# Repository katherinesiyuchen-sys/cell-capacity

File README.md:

# Cell Capacity Tester
An Arduino-based constant-current discharge tester for 18650 lithium cells. It pulls a selected/controlled current out of a cell and 
integrates that current over time to compute the cell's true capacity in mAh, with live readout on an OLED and automatic thermal cutoff for safety.

## How it works
The circuitry is a constant-current electronic load with an op-amp continuously adjusts a MOSFET's gate voltage to hold a selected discharge current steady 
regardless of the cell's falling voltage. By integrating that known current over time, the firmware accumulates total charge delivered, the cell's capacity, by multiplying the time and current.

## Circuit Overview
### Power system
BT1 (the 18650 cell) is the sole power source at ~3.6–4.2 V. Current flows from the positive terminal through **F1** (4 A resettable polyfuse) 
and **D1** (Schottky diode, low forward drop, blocks reverse insertion) onto the batt+ net. 
**C1 (100 nF)** and **C2 (220 µF)** in parallel stabilize batt+, where C2 absorbs voltage sags when the MOSFET draws heavy current, C1 filters high-frequency noise.

The Arduino is powered from USB (VUSB) +5V rail, and its 3V3 pin supplies the +3.3 V rail for the OLED.

### Constant-current discharge
- **Q1 (IRLZ44N)**: logic-level MOSFET in series with the load, acting as a variable resistor controlled by gate voltage. Fully on at 3.3–5 V, so it's directly Arduino-drivable.
- **R4A & R4B**: two 1 Ω / 10 W resistors in parallel (0.5 Ω total) as the sense/load resistors. All discharge current flows through them; voltage across them = I × 0.5 Ω.
- **U1A (LM358)**: op-amp in the feedback loop:
  - '–' input (pin 2): actual voltage across the load resistors (i.e. actual current)
  - '+' input (pin 3): filtered PWM from Arduino A2 (target current)
  - The op-amp drives the gate to null the difference: if actual current is too low the gate rises (MOSFET opens more); too high and it closes slightly.
- **R7 (470 Ω)** between op-amp output and gate damps high-frequency oscillation.
- **R3 / C3** form a low-pass RC filter (τ = 10k × 100 n = 1 ms) that smooths the A2 PWM into a steady DC target voltage.

### Current setting
**SW1 (D14)** and **SW2 (D15)** are pulled up to +5 V through R5/R6. Pressing a button pulls the pin to GND; the Arduino detects the falling edge and increases or decreases the A2 PWM duty cycle, 
which changes the target voltage at the op-amp and therefore the set current. SW1 is UP/START — it also begins the test.

### Temperature sensing
**TH1 (10k NTC thermistor)** forms a voltage divider with R2 (10k):
```
TEMP = 5 V × R2 / (R2 + TH1)
```
The Arduino reads TEMP on **A0**. As temperature rises, TH1's resistance drops and TEMP rises. Firmware uses this to cut off the test above a safe threshold. 
Mount TH1 as close to the battery holder as possible so it can be bent to contact the cell.

### OLED display (DS1)
128×64 I²C OLED powered from 3.3 V and displays voltage, current, temperature, and accumulated mAh live during the test.

### Buzzer
Driven directly by the Arduino, beeps on test start, end, and fault.

### Op-amp protection
The LM358 is a dual op-amp. U1A does the constant-current control; the unused sections are wired as unity-gain followers with negative feedback so their inputs aren't left floating 
(floating inputs can be driven to the rails by EMI, causing excess current draw and rail instability). C4 filters VCC into the op-amp.

## Bill of Materials
Full BOM: [Google Sheets](https://docs.google.com/spreadsheets/d/1DATSQ3IbzevVbkfX_8bRBYmYYDkdU8qtv9zlPYZS3Pw/edit?usp=sharing)

All components are sourced from **DigiKey** except the **OLED screen**, which is purchased from Amazon.

## License

Licensed under the [Apache License 2.0](LICENSE).

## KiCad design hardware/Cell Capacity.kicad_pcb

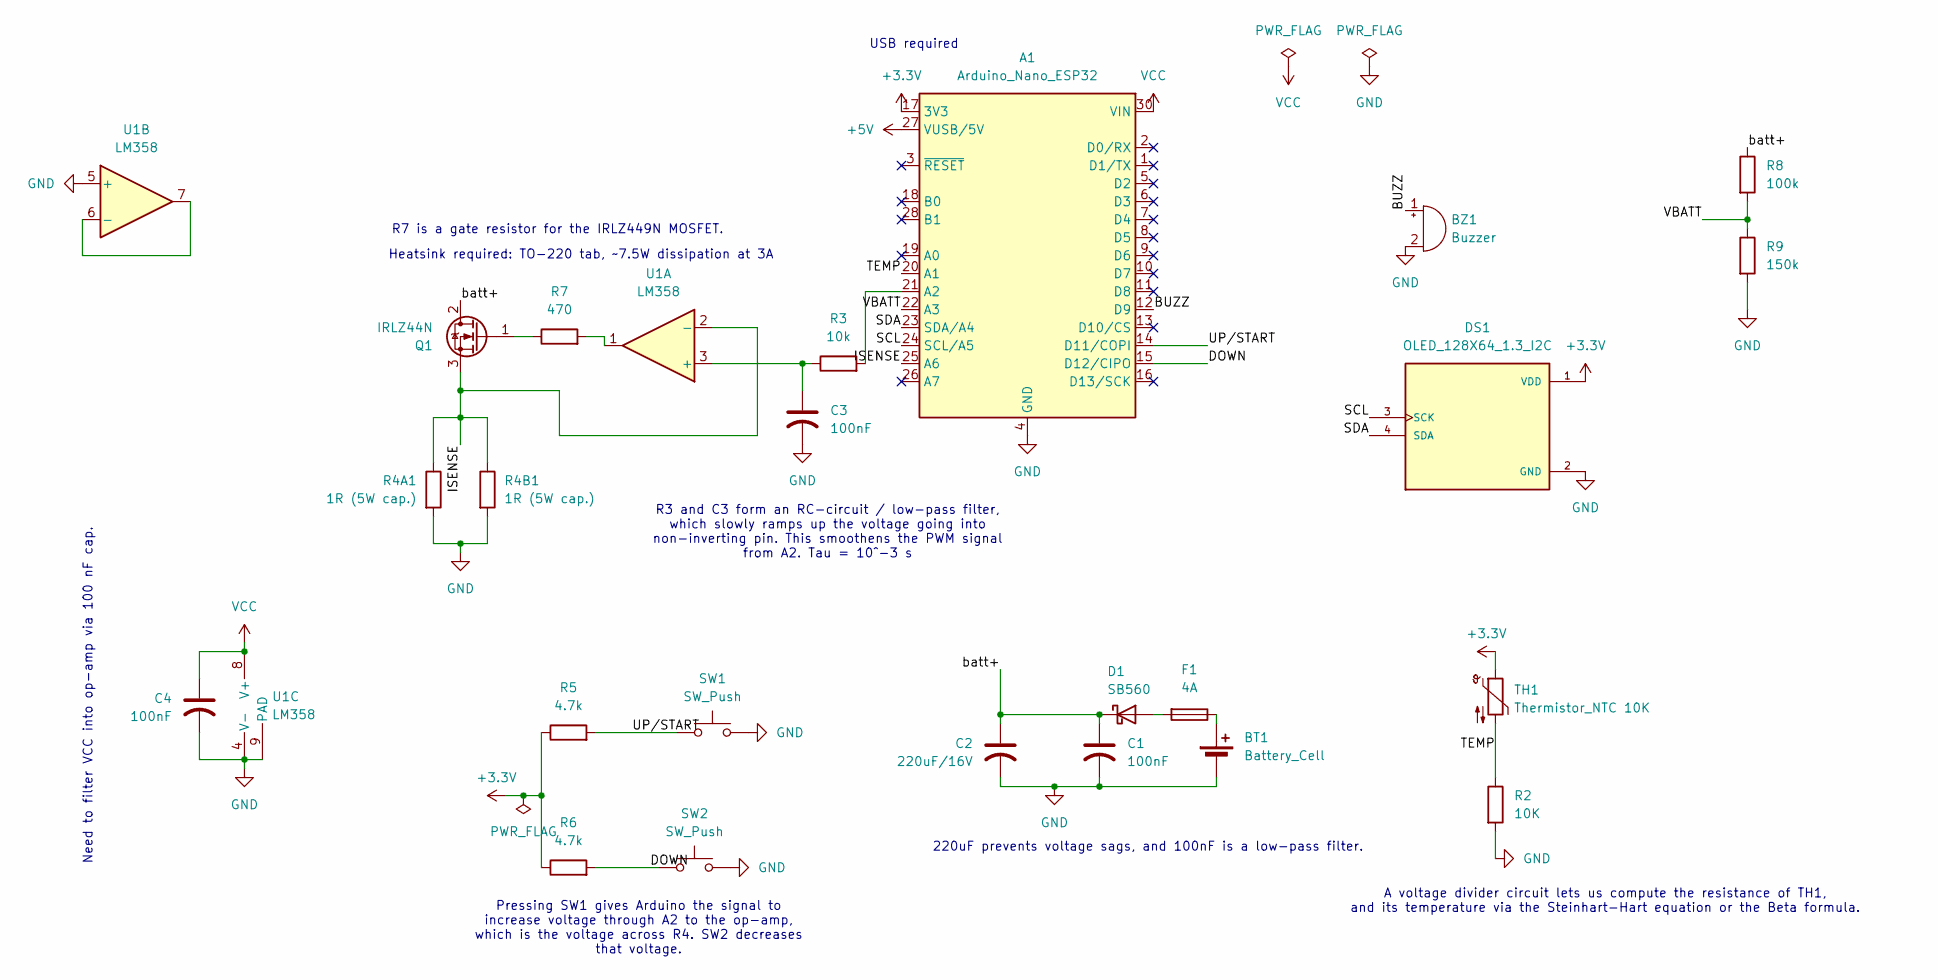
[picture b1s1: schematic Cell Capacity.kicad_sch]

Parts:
A1: Arduino_Nano_ESP32; Arduino_Nano
BT1: Battery_Cell; BatteryHolder_MPD_BK-18650-PC2
BZ1: Buzzer; Buzzer_12x9.5RM7.6
C1, C3, C4: 100nF; C_0603_1608Metric
C2: 220uF/16V; CP_Radial_D6.3mm_P2.50mm
D1: SB560; D_DO-41_SOD81_P10.16mm_Horizontal
DS1: OLED_128X64_1.3_I2C; PinHeader_1x04_P2.54mm_Vertical; PARTREV NA
F1: 4A; R_Axial_DIN0207_L6.3mm_D2.5mm_P10.16mm_Horizontal
Q1: IRLZ44N; TO-220-3_Vertical
R2: 10K; R_0603_1608Metric
R3: 10k; R_0603_1608Metric
R4A1, R4B1: 1R (5W cap.); R_Axial_Power_L25.0mm_W9.0mm_P30.48mm
R5, R6: 4.7k; R_0603_1608Metric
R7: 470; R_0603_1608Metric
R8: 100k; R_0603_1608Metric
R9: 150k; R_0603_1608Metric
SW1, SW2: SW_Push; SW_PUSH_6mm
TH1: Thermistor_NTC 10K; R_Axial_DIN0207_L6.3mm_D2.5mm_P7.62mm_Horizontal
U1: LM358; SOIC-8-1EP_3.9x4.9mm_P1.27mm_EP2.29x3mm

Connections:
+3.3V: A1.17 (3V3), DS1.1 (VDD), R5.1, R6.1, TH1.1; also elsewhere on the board
+5V: A1.27 (VUSB/5V)
/BUZZ: A1.12 (D9), BZ1.1 (+)
/DOWN: A1.15 (D12/CIPO), R6.2, SW2.1
/ISENSE: A1.25 (A6), Q1.3 (S), R4A1.1, R4B1.1, U1.2 (-)
/SCL: A1.24 (SCL/A5), DS1.3 (SCK); also elsewhere on the board
/SDA: A1.23 (SDA/A4), DS1.4 (SDA); also elsewhere on the board
/TEMP: A1.20 (A1), R2.1, TH1.2
/UP/START: A1.14 (D11/COPI), R5.2, SW1.1
/VBATT: A1.22 (A3), R8.2, R9.1
/batt+: C1.1, C2.1, D1.1 (K), Q1.2 (D), R8.1
GND: A1.4 (GND), A1.29 (GND), BT1.2 (-), BZ1.2 (-), C1.2, C2.2, C3.2, C4.2, DS1.2 (GND), R2.2, R4A1.2, R4B1.2, R9.2, SW1.2, SW2.2, U1.4 (V-), U1.5 (+), U1.9 (PAD); also elsewhere on the board
unnamed: A1.21 (A2), R3.2
unnamed: BT1.1 (+), F1.1
unnamed: D1.2 (A), F1.2
unnamed: Q1.1 (G), R7.1
unnamed: R7.2, U1.1
unnamed: C3.1, R3.1, U1.3 (+)
unnamed: U1.6 (-), U1.7
VCC: A1.30 (VIN), C4.1, U1.8 (V+)

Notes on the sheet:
Pressing SW1 gives Arduino the signal to increase voltage through A2 to the op-amp, which is the voltage across R4. SW2 decreases that voltage.
220uF prevents voltage sags, and 100nF is a low-pass filter.
R7 is a gate resistor for the IRLZ449N MOSFET.
R3 and C3 form an RC-circuit / low-pass filter, which slowly ramps up the voltage going into non-inverting pin. This smoothens the PWM signal from A2. Tau = 10^-3 s
USB required
Need to filter VCC into op-amp via 100 nF cap.
A voltage divider circuit lets us compute the resistance of TH1, and its temperature via the Steinhart-Hart equation or the Beta formula.
Heatsink required: TO-220 tab, ~7.5W dissipation at 3A

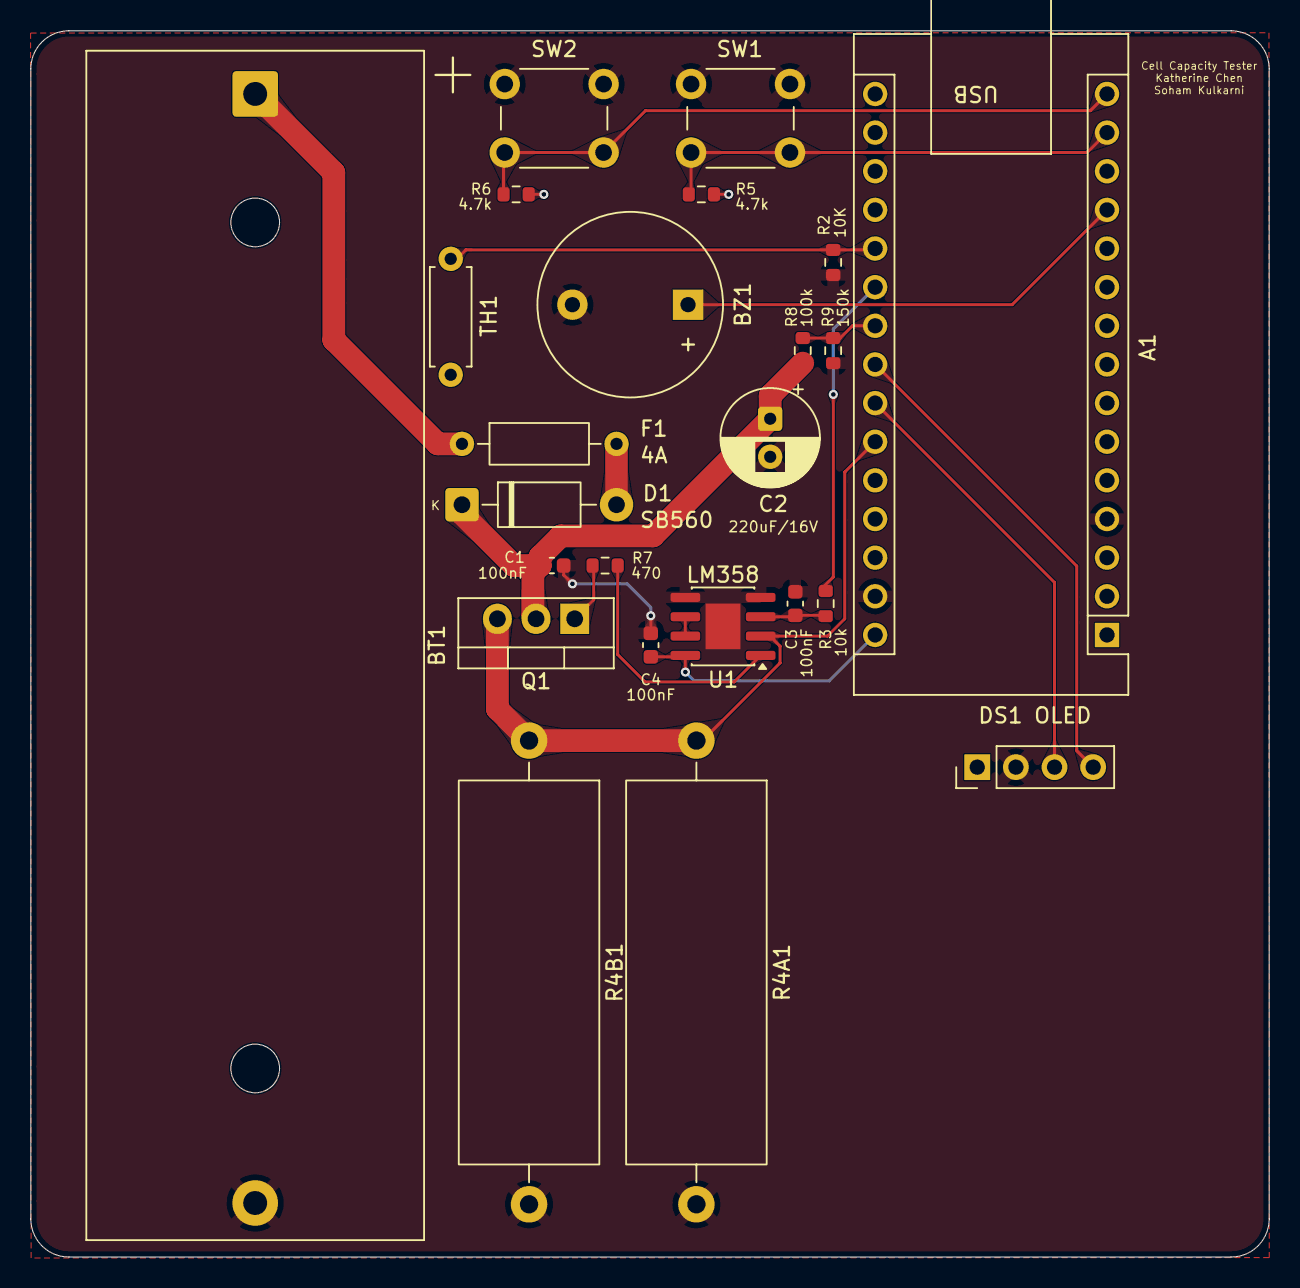
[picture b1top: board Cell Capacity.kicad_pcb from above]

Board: 2 copper layers, 81.4 x 80.6 mm, 24 parts (0 on the bottom side), 19 nets.

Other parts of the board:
DS1 OLED: OLED_128X64_1.3_I2C; PinHeader_1x04_P2.54mm_Vertical

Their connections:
+3.3V: DS1 OLED.1 (VDD); also elsewhere on the board
/SCL: DS1 OLED.3 (SCK); also elsewhere on the board
/SDA: DS1 OLED.4 (SDA); also elsewhere on the board
GND: DS1 OLED.2 (GND); also elsewhere on the board

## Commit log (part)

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2026-06-16 layout iter2
2026-06-17 misc fix
